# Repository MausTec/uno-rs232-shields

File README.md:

# Arduino RS232 Shields

This repository contains DTE and DCE shields for the Arduino Uno and compatible devices. These shields use the hardware
serial ports and provide a 9 pin serial connector for interfacing with older electronics. Each shield has a few
variants:

- Standard Variant: RS232 exits the back (notch side) of the Arduino
- Reverse Variant: RS232 exits the front (USB side) of the Arduino

## Are these for sale?

Oh you betcha! DIY Kits and assembled shields will be available on [maustec.io](https://maustec.io).

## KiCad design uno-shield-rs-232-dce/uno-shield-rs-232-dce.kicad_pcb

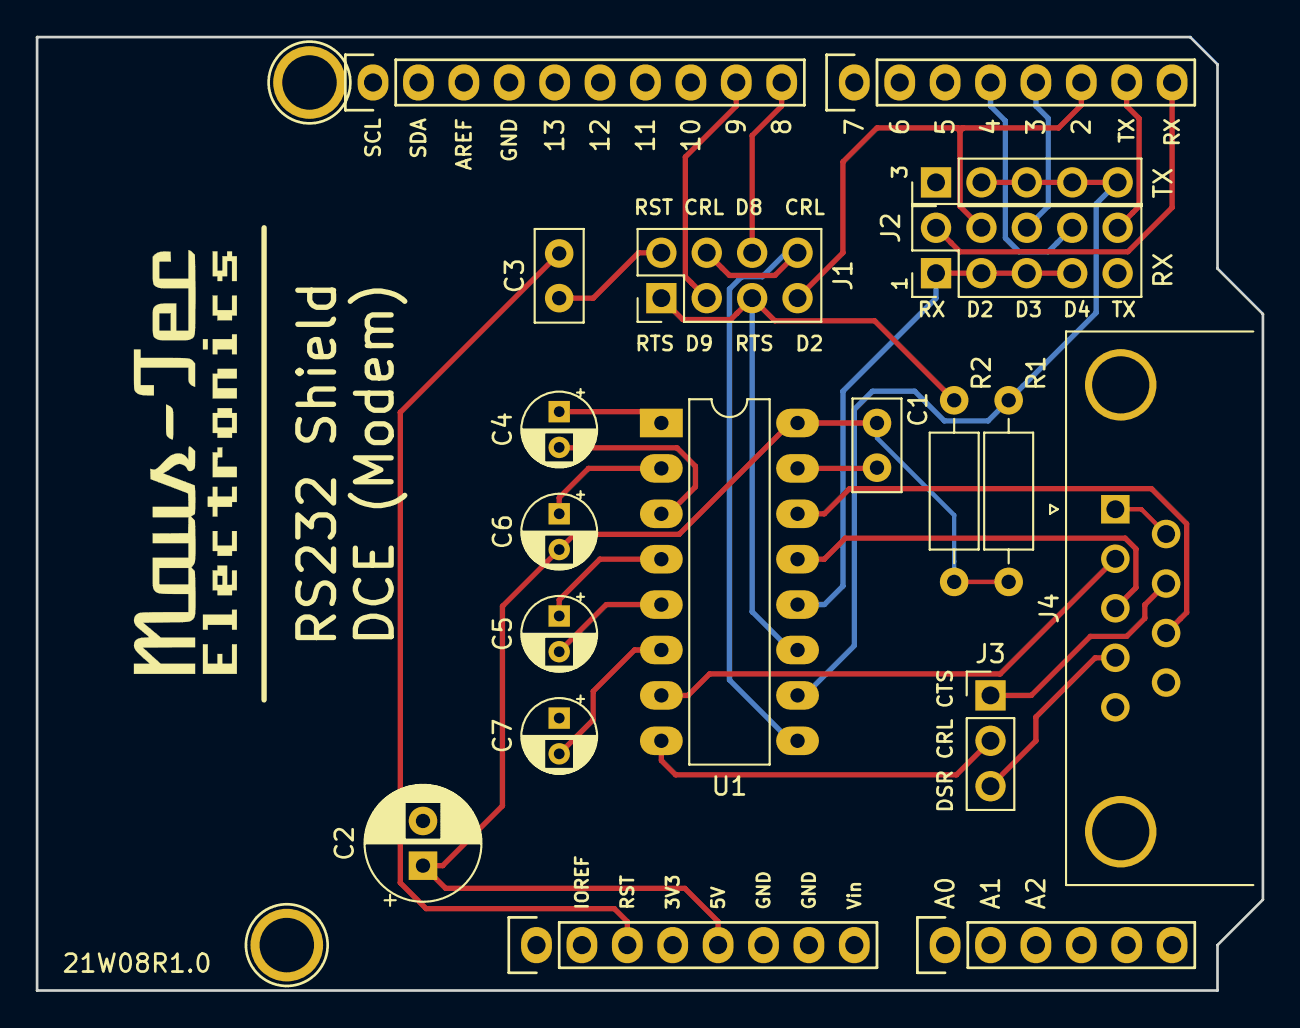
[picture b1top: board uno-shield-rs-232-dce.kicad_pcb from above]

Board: 2 copper layers, 68.6 x 53.3 mm, 21 parts (0 on the bottom side), 28 nets.

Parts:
C1, C3: 0.1u; C_Disc_D5.0mm_W2.5mm_P2.50mm
C2: 10u; CP_Radial_D6.3mm_P2.50mm
C4, C5, C6, C7: 1u; CP_Radial_D4.0mm_P2.00mm
J1: Ctrl Route; PinHeader_2x04_P2.54mm_Vertical
J2: RX Route; PinHeader_2x05_P2.54mm_Vertical
J3: DSR/CTS; PinHeader_1x03_P2.54mm_Vertical
J4: DB9_Female; DSUB-9_Female_Horizontal_P2.77x2.84mm_EdgePinOffset4.94mm_H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
J5: TX Route; PinHeader_1x05_P2.54mm_Vertical
P1: Power; Socket_Strip_Arduino_1x08
P2: Analog; Socket_Strip_Arduino_1x06
P3: Digital; Socket_Strip_Arduino_1x10
P4: Digital; Socket_Strip_Arduino_1x08
P5, P7: CONN_01X01; Arduino_1pin
R1, R2: 10k; R_Axial_DIN0207_L6.3mm_D2.5mm_P10.16mm_Horizontal
U1: MAX232; DIP-16_W7.62mm_LongPads

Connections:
+5V: C1.1, C2.1, C6.2, P1.5, R1.1, R2.1, U1.16
/CTRL: J3.2, U1.8
/CTS: J3.1, J4.7
/DCD: J4.1, J4.6
/DSR: J3.3, J4.4
/RTS: J4.8, U1.14
/RXD: J4.3, U1.13
/TXD: J4.2, U1.7
/UCTRL: J1.4, J1.8, U1.9
/URTS: J1.1, J1.5, R2.2, U1.11
D2: J1.7, J2.4, P4.6
D3: J2.6, P4.5
D4: J2.8, P4.4
D8: J1.6, P3.10
D9: J1.3, P3.9
GND: C1.2, C2.2, C7.1, J4.5, P1.6, P1.7, P3.4, U1.15
unnamed: C3.1, J1.2
unnamed: C4.1, U1.1
unnamed: C4.2, U1.3
unnamed: C5.1, U1.4
unnamed: C5.2, U1.5
unnamed: C6.1, U1.2
unnamed: C7.2, U1.6
RST: C3.2, P1.3
RX: J2.2, P4.8
TX: J2.10, P4.7
URX: J2.1, J2.3, J2.5, J2.7, U1.12
UTX: J5.2, J5.3, J5.4, J5.5, R1.2, U1.10

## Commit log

2021-02-27 Add DTE shield.
2021-02-27 Add DTE-Reverse
2021-02-27 Moved that PDF
2021-02-28 Adjust DTE shield to allow UART routing.
2021-02-28 Propagate signal routing changes to DTE-R shield.
2021-02-28 Add DCE revision.
2021-02-28 Add DCE reverse revision.
2021-02-28 Generate gerbers locally.
